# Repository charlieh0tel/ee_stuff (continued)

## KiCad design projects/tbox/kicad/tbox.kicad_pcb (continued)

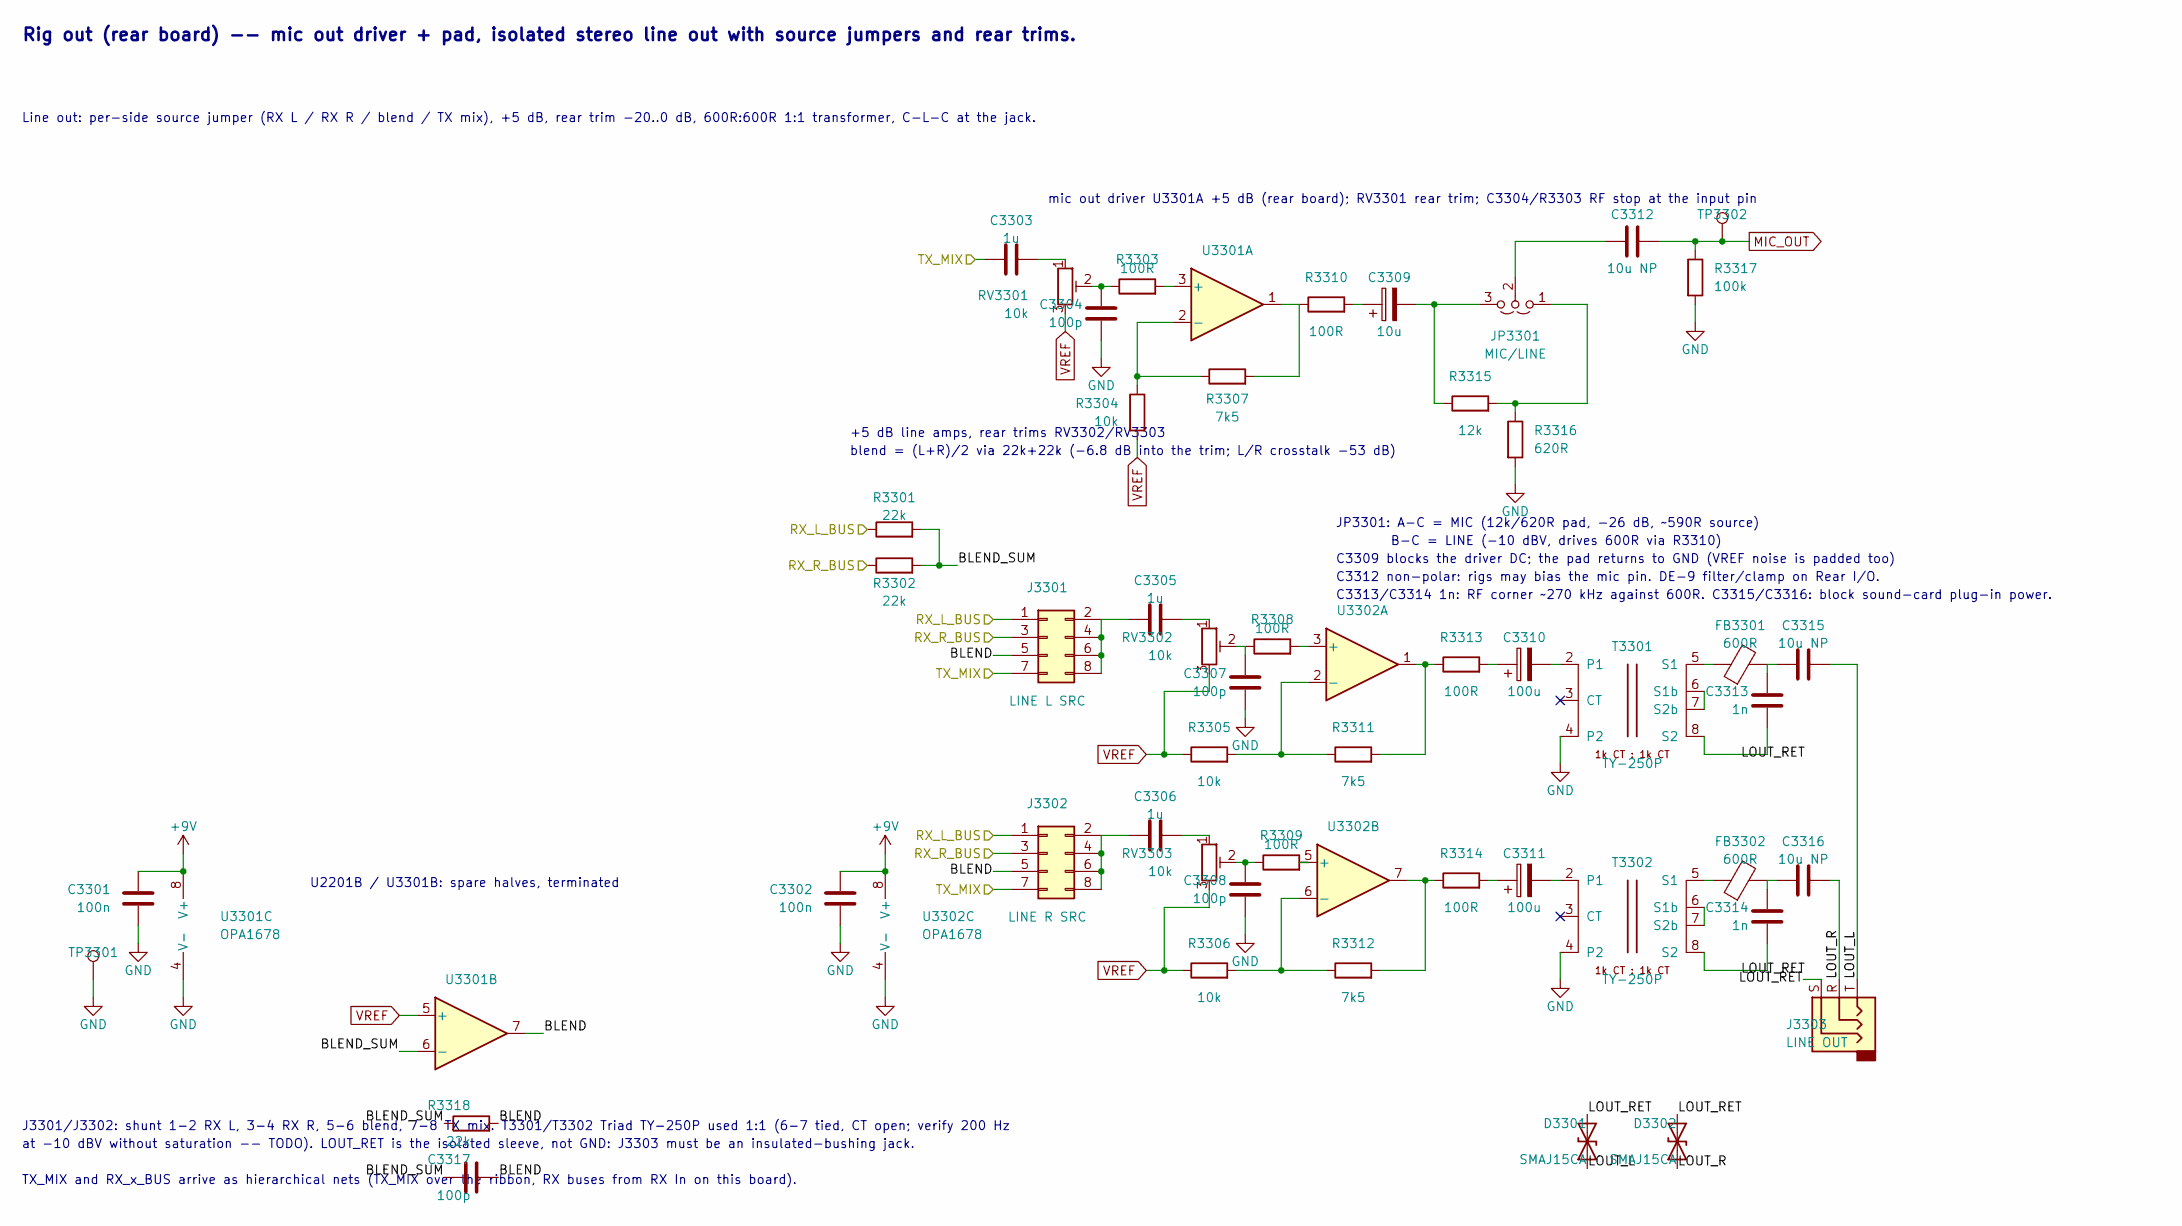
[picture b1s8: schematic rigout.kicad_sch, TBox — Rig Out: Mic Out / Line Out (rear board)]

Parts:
C3301, C3302: 100n; C_0603_1608Metric
C3303, C3305, C3306: 1u; C_0603_1608Metric
C3304, C3307, C3308, C3317: 100p; C_0603_1608Metric
C3309: 10u; CP_Elec_5x5.4
C3310, C3311: 100u; CP_Elec_6.3x7.7
C3312, C3315, C3316: 10u NP; C_1206_3216Metric
C3313, C3314: 1n; C_0603_1608Metric
D3301, D3302: SMAJ15CA; D_SMA; MPN SMAJ15CA
FB3301, FB3302: 600R; L_0805_2012Metric
J3301: LINE L SRC; PinHeader_2x04_P2.54mm_Vertical
J3302: LINE R SRC; PinHeader_2x04_P2.54mm_Vertical
J3303: LINE OUT; Jack_3.5mm_CUI_SJ1-3533NG_Horizontal; MPN SJ1-3533NG
JP3301: MIC/LINE; PinHeader_1x03_P2.54mm_Vertical
R3301, R3302, R3318: 22k; R_0603_1608Metric
R3303, R3308, R3309, R3310, R3313, R3314: 100R; R_0603_1608Metric
R3304, R3305, R3306: 10k; R_0603_1608Metric
R3307, R3311, R3312: 7k5; R_0603_1608Metric
R3315: 12k; R_0603_1608Metric
R3316: 620R; R_0603_1608Metric
R3317: 100k; R_0603_1608Metric
RV3301, RV3302, RV3303: 10k; Potentiometer_Bourns_3386W_Horizontal; MPN 3386W-1-103LF
T3301, T3302: TY-250P; Transformer_Triad_TY-250P; MPN TY-250P
TP3301: GND; TestPoint_Keystone_5015_Micro_Mini; MPN 5015
TP3302: MIC_OUT; TestPoint_Keystone_5015_Micro_Mini; MPN 5015
U3301, U3302: OPA1678; SOIC-8_3.9x4.9mm_P1.27mm; MPN OPA1678IDR

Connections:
+9V: C3301.1, C3302.1, U3301.8 (V+), U3302.8 (V+); also elsewhere on the board
/RX_L_BUS: J3301.1, J3302.1, R3301.1; also elsewhere on the board
/RX_R_BUS: J3301.3, J3302.3, R3302.1; also elsewhere on the board
/Rear Board/Rig Out/BLEND: C3317.2, J3301.5, J3302.5, R3318.2, U3301.7
/Rear Board/Rig Out/LOUT_L: C3315.2, D3301.1 (A1), J3303.T
/Rear Board/Rig Out/LOUT_R: C3316.2, D3302.1 (A1), J3303.R
/Rear Board/Rig Out/LOUT_RET: C3313.2, C3314.2, D3301.2 (A2), D3302.2 (A2), J3303.S, T3301.8 (S2), T3302.8 (S2)
/TX_MIX: C3303.1, J3301.7, J3302.7; also elsewhere on the board
MIC_OUT: C3312.2, R3317.1, TP3302.1 (1_1); also elsewhere on the board
unnamed: C3303.2, RV3301.1
unnamed: C3304.1, R3303.1, RV3301.2
unnamed: C3305.2, RV3302.1
unnamed: C3306.2, RV3303.1
unnamed: C3307.1, R3308.1, RV3302.2
unnamed: C3308.1, R3309.1, RV3303.2
unnamed: C3309.1, R3310.2
unnamed: C3310.1, R3313.2
unnamed: C3311.1, R3314.2
unnamed: C3313.1, C3315.1, FB3301.2
unnamed: C3314.1, C3316.1, FB3302.2
unnamed: C3305.1, J3301.2, J3301.4, J3301.6, J3301.8
unnamed: C3306.1, J3302.2, J3302.4, J3302.6, J3302.8
unnamed: JP3301.1 (A), R3315.2, R3316.1
unnamed: C3309.2, JP3301.3 (B), R3315.1
unnamed: C3312.1, JP3301.2 (C)
unnamed: R3307.2, R3310.1, U3301.1
unnamed: R3311.2, R3313.1, U3302.1
unnamed: R3312.2, R3314.1, U3302.7
unnamed: C3310.2, T3301.2 (P1)
unnamed: FB3301.1, T3301.5 (S1)
unnamed: T3301.6 (S1b), T3301.7 (S2b)
unnamed: C3311.2, T3302.2 (P1)
unnamed: FB3302.1, T3302.5 (S1)
unnamed: T3302.6 (S1b), T3302.7 (S2b)
unnamed: R3303.2, U3301.3 (+)
unnamed: R3304.1, R3307.1, U3301.2 (-)
unnamed: R3308.2, U3302.3 (+)
unnamed: R3305.2, R3311.1, U3302.2 (-)
unnamed: R3309.2, U3302.5 (+)
unnamed: R3306.2, R3312.1, U3302.6 (-)

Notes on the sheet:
J3301/J3302: shunt 1-2 RX L, 3-4 RX R, 5-6 blend, 7-8 TX mix. T3301/T3302 Triad TY-250P used 1:1 (6-7 tied, CT open; verify 200 Hz
at -10 dBV without saturation -- TODO). LOUT_RET is the isolated sleeve, not GND: J3303 must be an insulated-bushing jack.
B-C = LINE (-10 dBV, drives 600R via R3310)
C3312 non-polar: rigs may bias the mic pin. DE-9 filter/clamp on Rear I/O.
blend = (L+R)/2 via 22k+22k (-6.8 dB into the trim; L/R crosstalk -53 dB)
U2201B / U3301B: spare halves, terminated
+5 dB line amps, rear trims RV3302/RV3303
Rig out (rear board) -- mic out driver + pad, isolated stereo line out with source jumpers and rear trims.
TX_MIX and RX_x_BUS arrive as hierarchical nets (TX_MIX over the ribbon, RX buses from RX In on this board).
mic out driver U3301A +5 dB (rear board); RV3301 rear trim; C3304/R3303 RF stop at the input pin
Line out: per-side source jumper (RX L / RX R / blend / TX mix), +5 dB, rear trim -20..0 dB, 600R:600R 1:1 transformer, C-L-C at the jack.
C3309 blocks the driver DC; the pad returns to GND (VREF noise is padded too)
C3313/C3314 1n: RF corner ~270 kHz against 600R. C3315/C3316: block sound-card plug-in power.
JP3301: A-C = MIC (12k/620R pad, -26 dB, ~590R source)

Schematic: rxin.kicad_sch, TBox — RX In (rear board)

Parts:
C3401, C3402: 10u X7R 25V; C_1206_3216Metric; MPN GRM31CR71E106KA12L
C3403, C3404: 47u; CP_Elec_6.3x5.4
C3405, C3406: 100p; C_0603_1608Metric
C3407: 100n; C_0603_1608Metric
D3401, D3402, D3403, D3404: 1N4148W; D_SOD-123; MPN 1N4148W
R3403, R3404: 2k2; R_0603_1608Metric
R3405, R3406: 10k; R_0603_1608Metric
R3407, R3408: 100k; R_0603_1608Metric
R3409, R3410: 47k; R_0603_1608Metric
R3411, R3412: 100R; R_0603_1608Metric
RV3401, RV3402: 10k; Potentiometer_Bourns_3386W_Horizontal; MPN 3386W-1-103LF
TP3401: RX_L_BUS; TestPoint_Keystone_5015_Micro_Mini; MPN 5015
TP3402: RX_R_BUS; TestPoint_Keystone_5015_Micro_Mini; MPN 5015
U3401: OPA1678; SOIC-8_3.9x4.9mm_P1.27mm; MPN OPA1678IDR

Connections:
+9V: C3407.1, D3401.1 (K), D3403.1 (K), U3401.8 (V+); also elsewhere on the board
/RX_L_BUS: R3411.2, TP3401.1 (1_1); also elsewhere on the board
/RX_R_BUS: R3412.2, TP3402.1 (1_1); also elsewhere on the board
/Rear Board/RX In/RXA_AMP: C3405.1, D3401.2 (A), D3402.1 (K), R3403.2, R3407.2, U3401.3 (+)
/Rear Board/RX In/RXB_AMP: C3406.1, D3403.2 (A), D3404.1 (K), R3404.2, R3408.2, U3401.5 (+)
unnamed: C3401.1, R3403.1
unnamed: C3401.2, RV3401.2
unnamed: C3402.1, R3404.1
unnamed: C3402.2, RV3402.2
unnamed: C3403.1, R3405.1
unnamed: C3404.1, R3406.1
unnamed: R3409.2, R3411.1, U3401.1
unnamed: R3410.2, R3412.1, U3401.7
unnamed: R3405.2, R3409.1, U3401.2 (-)
unnamed: R3406.2, R3410.1, U3401.6 (-)
RX_L_IN: RV3401.1; also elsewhere on the board
RX_R_IN: RV3402.1; also elsewhere on the board

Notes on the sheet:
Max ~-0.4 dBV open (17 mW/32R, 22 mW/16R through the 10R build-out; one headset per position). 3.5 mm, 1/4" and the TRRS phones side (J1103/J1303 on the preamp sheets, via PH_x_L/R) are paralleled.
RX in (rear board) -- 10k bridging load, rear trims, +15 dB buffers -> RX_L_BUS / RX_R_BUS.
+15 dB (1 + 47k/10k), unity at DC (C3403/C3404); trims to GND, +in biased to VREF via 100k (VREF noise gain ~1); R3403/C3405 RF stop at the pin
RX in: the rear 10k trim to GND is the bridging load (hot phones-jack sources are simply trimmed down), AC-coupled into a +15 dB buffer -> RX_L_BUS / RX_R_BUS at -15 dBV.
Mono rig cables tie RX L and RX R at the DE-9 (Rear I/O sheet, with the filter/clamp).

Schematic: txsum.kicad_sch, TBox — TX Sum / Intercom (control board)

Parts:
C2201, C2202: 1u; C_0603_1608Metric
C2203, C2205: 100n; C_0603_1608Metric
C2204: 47p; C_0603_1608Metric
D2201: IC LED; LED_0805_2012Metric
Q2201: MMBT3904; SOT-23; MPN MMBT3904
Q2202: 2N7002; SOT-23; MPN 2N7002
R2201, R2202, R2203, R2204, R2206, R2208, R2209: 10k; R_0603_1608Metric
R2205: 20k; R_0603_1608Metric
R2207: 100R; R_0603_1608Metric
R2210: 2k2; R_0805_2012Metric
R2211: 100k; R_0603_1608Metric
RV2201, RV2202: 10k; Potentiometer_Alpha_RD901F-40-00D_Single_Vertical; MPN RD901F-40-15R1-A10K
SW2201: INTERCOM; SW_Push_2P1T_Toggle_CK_PVA1xxH2xxxxxxV2; MPN PVA1OAH2xxxxxxV2 (OA = momentary; heigh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
TP2201: TX_MIX; TestPoint_Keystone_5015_Micro_Mini; MPN 5015
TP2202: CH_A_OUT; TestPoint_Keystone_5015_Micro_Mini; MPN 5015
TP2203: CH_B_OUT; TestPoint_Keystone_5015_Micro_Mini; MPN 5015
U2201: OPA1678; SOIC-8_3.9x4.9mm_P1.27mm; MPN OPA1678IDR

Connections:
+9V: C2205.1, R2201.1, R2208.1, U2201.8 (V+); also elsewhere on the board
/Control Board/TX Sum / Intercom/CH_A_OUT: C2201.1, RV2201.2, TP2202.1 (1_1)
/Control Board/TX Sum / Intercom/CH_B_OUT: C2202.1, RV2202.2, TP2203.1 (1_1)
/PRE_A_OUT: RV2201.1; also elsewhere on the board
/PRE_B_OUT: RV2202.1; also elsewhere on the board
/PTT_ACTIVE: R2206.1; also elsewhere on the board
/TX_MIX: R2211.1, TP2201.1 (1_1); also elsewhere on the board
unnamed: C2201.2, R2202.1
unnamed: C2202.2, R2203.1
unnamed: C2203.1, R2201.2, R2204.1, SW2201.2
unnamed: C2204.2, R2205.2, R2207.1, U2201.1
unnamed: D2201.2 (A), R2210.2
unnamed: D2201.1 (K), Q2202.3 (D)
unnamed: Q2201.1 (B), R2204.2, R2206.2
unnamed: Q2202.1 (G), R2209.2
unnamed: C2204.1, R2202.2, R2203.2, R2205.1, U2201.2 (-)
unnamed: U2201.6 (-), U2201.7
TX_MON: R2207.2; also elsewhere on the board

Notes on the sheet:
R2207 isolates the cap load
post-mute TX mix (line level; crosses to rear board)
Intercom: momentary, mutes TX downstream of the monitor tap; locked out while PTT_ACTIVE=1 (Keying Logic sheet). Control lines are DC logic 0/+9V, active high.
+6 dB inverting sum (Rf/Rin = 2)
Levels (LEVELS.md): level-pot wipers -21 dBV -> sum +6 dB -> -15 dBV. Mic out: +5 dB driver, rear trim -20..0 dB, MIC pad -26 dB (~590R source) or LINE direct.
Level pots RV2201/RV2202 (top panel) live here: PRE_x_OUT arrives at line level over the ribbon; the wiper feeds the sum locally.
Bus order: sum -> TX_MON (monitor pots, Monitor/Phones sheet) -> intercom mute -> TX_MIX -> mic out pad / line out TX tap.
LEVEL A (top panel), audio taper; -21 dBV at design centre
LEVEL B (top panel), audio taper; -21 dBV at design centre
LED from the raw rail (droppers), never from +9V
Hierarchical: PRE_x_OUT from the front board (ribbon), TX_MIX to the rear board, PTT_ACTIVE from Keying Logic.
TX sum / intercom (control board) -- channel level pots, summing amp, monitor tap, intercom mute + logic.
IC_MUTE = NOT(button up OR PTT_ACTIVE): pressed & not keyed -> mute

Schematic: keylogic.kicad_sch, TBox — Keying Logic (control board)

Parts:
C2101, C2102: 100n; C_0603_1608Metric
D2101: TX; LED_0805_2012Metric
D2102: PTT A; LED_0805_2012Metric
D2103, D2104, D2105, D2106, D2109, D2110, D2111, D2112, D2113, D2114, D2115, D2116, D2120, D2121: 1N4148W; D_SOD-123; MPN 1N4148W
D2107: PTT B; LED_0805_2012Metric
D2108: MUTE A; LED_0805_2012Metric
D2117: MUTE B; LED_0805_2012Metric
D2118: PWR; LED_0805_2012Metric
JP2101, JP2102: PTT GATE; PinHeader_1x02_P2.54mm_Vertical
Q2101, Q2102, Q2103, Q2104, Q2105, Q2106, Q2107, Q2108, Q2109: 2N7002; SOT-23; MPN 2N7002
R2101, R2103, R2107, R2108, R2109, R2113, R2118, R2122: 10k; R_0603_1608Metric
R2102, R2106, R2110, R2114, R2119, R2120: 2k2; R_0805_2012Metric
R2104, R2105, R2115, R2116: 1k; R_0603_1608Metric
R2111, R2112: 2k2; R_0603_1608Metric
R2117: 47k; R_0603_1608Metric
SW2101: PTT A; SW_Push_2P1T_Toggle_CK_PVA1xxH2xxxxxxV2; MPN PVA1OAH2xxxxxxV2 (OA = momentary; heigh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
SW2102: PTT B; SW_Push_2P1T_Toggle_CK_PVA1xxH2xxxxxxV2; MPN PVA1OAH2xxxxxxV2 (OA = momentary; heigh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
SW2103: OVERRIDE; SW_Toggle_CK_7201_V-Bracket_Vertical; MPN 7203MD9V6BE
SW2104: MUTE A; SW_Push_2P1T_Toggle_CK_PVA1xxH2xxxxxxV2; MPN PVA1EEH2xxxxxxV2 (EE = push-push latchi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
SW2105: MUTE B; SW_Push_2P1T_Toggle_CK_PVA1xxH2xxxxxxV2; MPN PVA1EEH2xxxxxxV2 (EE = push-push latchi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
TP2101: PTT_ACTIVE; TestPoint_Keystone_5015_Micro_Mini; MPN 5015
TP2102: MUTE_A; TestPoint_Keystone_5015_Micro_Mini; MPN 5015
TP2103: MUTE_B; TestPoint_Keystone_5015_Micro_Mini; MPN 5015
TP2104: GND; TestPoint_Keystone_5015_Micro_Mini; MPN 5015

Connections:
+9V: D2103.1 (K), D2105.1 (K), R2111.1, R2112.1, R2115.1, R2116.1, R2122.1; also elsewhere on the board
/Control Board/Keying Logic/MUTE_HOLD: D2120.2 (A), D2121.2 (A), Q2108.3 (D), Q2109.1 (G), R2122.2
/Control Board/Keying Logic/OVR_A: D2111.2 (A), SW2103.6 (C)
/Control Board/Keying Logic/OVR_B: D2114.2 (A), SW2103.1 (A)
/Control Board/Keying Logic/PTT_A: D2109.2 (A), Q2104.3 (D), R2103.1, R2111.2, SW2103.2 (B)
/Control Board/Keying Logic/PTT_A_N: C2101.1, D2103.2 (A), D2104.1 (K), JP2101.1 (A), R2104.2, R2108.1
/Control Board/Keying Logic/PTT_B: D2110.2 (A), Q2105.3 (D), R2107.1, R2112.2, SW2103.5 (B)
/Control Board/Keying Logic/PTT_B_N: C2102.1, D2105.2 (A), D2106.1 (K), JP2102.1 (A), R2105.2, R2109.1
/MUTE_B: D2114.1 (K), D2115.1 (K), D2116.1 (K), D2121.1 (K), R2118.1, TP2103.1 (1_1); also elsewhere on the board
/PTT_ACTIVE: D2109.1 (K), D2110.1 (K), Q2109.3 (D), R2101.1, R2117.1, TP2101.1 (1_1); also elsewhere on the board
/PTT_A_IN: R2104.1, SW2101.2; also elsewhere on the board
/PTT_B_IN: R2105.1, SW2102.2; also elsewhere on the board
unnamed: D2101.2 (A), R2102.2
unnamed: D2101.1 (K), Q2101.3 (D)
unnamed: D2102.2 (A), R2106.2
unnamed: D2102.1 (K), Q2102.3 (D)
unnamed: D2107.2 (A), R2110.2
unnamed: D2107.1 (K), Q2103.3 (D)
unnamed: D2108.2 (A), R2114.2
unnamed: D2108.1 (K), Q2106.3 (D)
unnamed: D2112.2 (A), SW2104.2 (B)
unnamed: D2113.2 (A), JP2101.2 (B)
unnamed: D2115.2 (A), SW2105.2 (B)
unnamed: D2116.2 (A), JP2102.2 (B)
unnamed: D2117.2 (A), R2119.2
unnamed: D2117.1 (K), Q2107.3 (D)
unnamed: D2118.2 (A), R2120.2
unnamed: Q2101.1 (G), R2101.2
unnamed: Q2102.1 (G), R2103.2
unnamed: Q2103.1 (G), R2107.2
unnamed: Q2104.1 (G), R2108.2
unnamed: Q2105.1 (G), R2109.2
unnamed: Q2106.1 (G), R2113.2
unnamed: Q2107.1 (G), R2118.2
unnamed: R2115.2, SW2104.1 (A)
unnamed: R2116.2, SW2105.1 (A)
PWR_OK: Q2108.1 (G); also elsewhere on the board

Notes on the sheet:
INDICATORS: TX lamp (17 mA, prominent), per-channel PTT and MUTE, power. Intercom LED is on the TX Sum sheet.
both mutes on through D2120/D2121, PTT_ACTIVE shunted by Q2109, phones amps disabled.
Keying logic (control board) -- PTT inputs from the rear jacks + top-panel buttons, override / mute logic, indicators, power-on hold.
Logic (0/+9V, active high): PTT_x = keyed (2k2 pull-up, ~7.4 V loaded); PTT_ACTIVE = A or B (~6.8 V) -> 2N7002 open-drain to the rig, intercom lockout, TX lamp.
All LEDs run from the raw filtered rail so their step loads never touch the +9V analog rail.
Power-on / brown-out hold: PWR_OK (TPS3808, Supply sheet) low -> Q2108 raises MUTE_HOLD:
OVERRIDE (SW2103, on-off-on): A->B / centre OFF / B->A as marked on the top panel
JP2101/JP2102 (PTT GATE): mic live only while keyed
OVERRIDE (DPDT on-off-on, top panel): A->B keys the rig from A and mutes B; B->A mirror. MUTE_x = latching button OR override OR (JP70x: not keyed) OR power-on hold. All logic transistors are 2N7002 so no base current loads the logic highs.

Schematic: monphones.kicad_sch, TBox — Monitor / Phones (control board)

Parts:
C2401, C2402, C2408, C2409: 470u; CP_Elec_10x10.5
C2405, C2407: 220u; CP_Elec_8x10.5
C2406, C2410, C2413: 100n; C_0603_1608Metric
H2401: CHASSIS STUD; MountingHole_3.2mm_M3_Pad
NT2401: GND-CHASSIS tie; NetTie-2_SMD_Pad0.5mm
R2401, R2402, R2403, R2404, R2405, R2406, R2413, R2414, R2415, R2416, R2417, R2418: 10k; R_0603_1608Metric
R2407, R2408, R2419, R2420: 150k; R_0603_1608Metric
R2409, R2410, R2421, R2422: 3R3; R_0603_1608Metric
R2411, R2412, R2423, R2424: 4k7; R_0603_1608Metric
RV2401, RV2404: 10k dual; Potentiometer_Alpha_RD902F-40-00D_Dual_Vertical; MPN RD902F-40-15R1-A10K
RV2402, RV2403: 10k; Potentiometer_Alpha_RD901F-40-00D_Single_Vertical; MPN RD901F-40-15R1-A10K
TP2401: GND; TestPoint_Keystone_5015_Micro_Mini; MPN 5015
U2401, U2403: OPA1622; Texas_DRC0010J; MPN OPA1622IDRCR
U2402: OPA1678; SOIC-8_3.9x4.9mm_P1.27mm; MPN OPA1678IDR

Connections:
+9V: C2405.1, C2406.1, C2407.1, C2410.1, C2413.1, U2401.2 (V+), U2402.8 (V+), U2403.2 (V+); also elsewhere on the board
/Control Board/Monitor / Phones/MON_A: R2402.1, R2404.1, U2402.1, U2402.2 (-)
/Control Board/Monitor / Phones/MON_B: R2414.1, R2416.1, U2402.6 (-), U2402.7
/PH_A_L: C2401.2, R2411.1; also elsewhere on the board
/PH_A_R: C2402.2, R2412.1; also elsewhere on the board
/PH_B_L: C2408.2, R2423.1; also elsewhere on the board
/PH_B_R: C2409.2, R2424.1; also elsewhere on the board
/RX_L_BUS: R2401.1, R2413.1; also elsewhere on the board
/RX_R_BUS: R2403.1, R2415.1; also elsewhere on the board
unnamed 80: C2401.1, R2409.2; also elsewhere on the board
unnamed 81: C2402.1, R2410.2; also elsewhere on the board
unnamed 82: C2408.1, R2421.2; also elsewhere on the board
unnamed 83: C2409.1, R2422.2; also elsewhere on the board
unnamed: R2401.2, R2402.2, RV2401.1
unnamed: R2403.2, R2404.2, RV2401.4
unnamed: R2407.2, R2409.1, U2401.9
unnamed: R2408.2, R2410.1, U2401.7
unnamed: R2413.2, R2414.2, RV2404.1
unnamed: R2415.2, R2416.2, RV2404.4
unnamed: R2419.2, R2421.1, U2403.9
unnamed: R2420.2, R2422.1, U2403.7
unnamed: RV2401.2, U2401.1 (+)
unnamed: R2405.1, R2407.1, U2401.10 (-)
unnamed: RV2401.5, U2401.5 (+)
unnamed: R2406.1, R2408.1, U2401.6 (-)
unnamed: RV2402.2, U2402.3 (+)
unnamed: RV2403.2, U2402.5 (+)
unnamed: RV2404.2, U2403.1 (+)
unnamed: R2417.1, R2419.1, U2403.10 (-)
unnamed: RV2404.5, U2403.5 (+)
unnamed: R2418.1, R2420.1, U2403.6 (-)
PWR_OK: U2401.8 (EN), U2403.8 (EN); also elsewhere on the board
TX_MON: RV2402.1, RV2403.1; also elsewhere on the board

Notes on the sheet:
Hierarchical: RX_x_BUS from the rear board (ribbon); PH_x_L/R to the front board (ribbon). TX_MON is board-local from TX Sum.
POSITION A
MON pots: front panel, per position
OPA1622: 150 mA output, drives 16R phones from 9 V; EN = PWR_OK (click-free enable), PAD = V-
RV2401/RV2404: dual-gang volume; all pots return to VREF (no DC on wipers).
Monitor: TX_MON (pre-intercom) -> front MON pot per position -> unity buffer -> MON_A / MON_B (off .. -15 dBV).
C2405/C2407: +9V bulk next to U2401/U2403 (class-B return current)
POSITION B
Monitor / phones (control board) -- MON pots and buffers, per-ear passive mix, VOL, NJM4556A headphone amps -> front-board jacks.
Each ear: RX side + MON summed passively (10k+10k into the 10k volume gang, -9.5 dB) -> NJM4556A +24 dB -> 10R -> 470u -> bead + 10n -> PH_x_L/R over the ribbon to the front-board jacks (sleeves to GND).

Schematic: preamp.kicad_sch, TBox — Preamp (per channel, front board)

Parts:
C1101, C1109: 1n; C_0603_1608Metric
C1102, C1107, C1108: 100n; C_0603_1608Metric
C1103: 1u; C_0603_1608Metric
C1104: 100p; C_0603_1608Metric
C1105, C1106: 47u; CP_Elec_6.3x5.4
FB1101, FB1102, FB1103: 600R; L_0805_2012Metric
J1101: MIC 3.5; Jack_3.5mm_Switchcraft_35RAPCxxH3_Horizontal; MPN 35RAPC2BH3
J1102: MIC 1/4; Jack_6.35mm_Neutrik_NRJ6HM-1-PRE_Horizontal; MPN NRJ6HM-1-PRE
J1103: HEADSET; Jack_3.5mm_CUI_SJ-43514_Horizontal; MPN SJ-43514
J1104: SPARE; JST_XH_B4B-XH-A_1x04_P2.50mm_Vertical; MPN B4B-XH-A
R1101, R1109: 2k2; R_0603_1608Metric
R1102: 47k; R_0603_1608Metric
R1103: 100R; R_0603_1608Metric
R1104: 430R; R_0603_1608Metric
R1105, R1107: 10k; R_0603_1608Metric
R1106: 3k3; R_0603_1608Metric
R1108: 100k; R_0603_1608Metric
TP1101: GND; TestPoint_Keystone_5015_Micro_Mini; MPN 5015
U1101: OPA1678; SOIC-8_3.9x4.9mm_P1.27mm; MPN OPA1678IDR
U1102: TS12A12511; MSOP-8_3x3mm_P0.65mm; MPN TS12A12511DGKR
U1103, U1104: SP724; SOT-23-6; MPN SP724AHTG

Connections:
+9V: C1107.1, C1108.1, J1104.4, U1101.8 (V+), U1102.4 (V+), U1103.5 (V+), U1104.5 (V+); also elsewhere on the board
/BIAS_A: C1102.1, J1104.2, R1101.1, R1109.1; also elsewhere on the board
/Front Board/PHJ_A_L: J1103.T, U1104.1 (IN1); also elsewhere on the board
/Front Board/PHJ_A_R: J1103.R1, U1104.3 (IN2); also elsewhere on the board
/Front Board/Preamp A/HS_MIC: FB1103.1, J1103.S, U1103.6 (IN4)
/Front Board/Preamp A/MIC: C1101.1, C1103.1, FB1101.2, FB1102.2, FB1103.2, J1104.1, R1101.2
/Front Board/Preamp A/MIC14T: FB1102.1, J1102.T, U1103.4 (IN3)
/Front Board/Preamp A/MIC35T: FB1101.1, J1101.T, U1103.1 (IN1)
/Front Board/Preamp A/MIC_R: C1109.1, J1101.R, R1109.2, U1103.3 (IN2)
/Front Board/Preamp A/Mute/IN: U1102.1 (COM); also elsewhere on the board
/GAIN_A_HI: R1108.1, U1102.6 (IN); also elsewhere on the board
unnamed: C1103.2, R1102.1, R1103.1
unnamed: C1105.1, R1104.2
unnamed: C1106.1, R1106.2
unnamed: C1104.1, R1103.2, U1101.3 (+)
unnamed: R1104.1, R1105.1, U1101.2 (-)
unnamed: R1105.2, U1101.1, U1101.5 (+), U1102.2 (NC)
unnamed: R1106.1, R1107.1, U1101.6 (-)
unnamed: R1107.2, U1101.7, U1102.8 (NO)

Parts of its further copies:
C1301, C1309: 1n; C_0603_1608Metric
C1302, C1307, C1308: 100n; C_0603_1608Metric
C1303: 1u; C_0603_1608Metric
C1304: 100p; C_0603_1608Metric
C1305, C1306: 47u; CP_Elec_6.3x5.4
FB1301, FB1302, FB1303: 600R; L_0805_2012Metric
J1301: MIC 3.5; Jack_3.5mm_Switchcraft_35RAPCxxH3_Horizontal; MPN 35RAPC2BH3
J1302: MIC 1/4; Jack_6.35mm_Neutrik_NRJ6HM-1-PRE_Horizontal; MPN NRJ6HM-1-PRE
J1303: HEADSET; Jack_3.5mm_CUI_SJ-43514_Horizontal; MPN SJ-43514
J1304: SPARE; JST_XH_B4B-XH-A_1x04_P2.50mm_Vertical; MPN B4B-XH-A
R1301, R1309: 2k2; R_0603_1608Metric
R1302: 47k; R_0603_1608Metric
R1303: 100R; R_0603_1608Metric
R1304: 430R; R_0603_1608Metric
R1305, R1307: 10k; R_0603_1608Metric
R1306: 3k3; R_0603_1608Metric
R1308: 100k; R_0603_1608Metric
TP1301: GND; TestPoint_Keystone_5015_Micro_Mini; MPN 5015
U1301: OPA1678; SOIC-8_3.9x4.9mm_P1.27mm; MPN OPA1678IDR
U1302: TS12A12511; MSOP-8_3x3mm_P0.65mm; MPN TS12A12511DGKR
U1303, U1304: SP724; SOT-23-6; MPN SP724AHTG

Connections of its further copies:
+9V: C1307.1, C1308.1, J1304.4, U1301.8 (V+), U1302.4 (V+), U1303.5 (V+), U1304.5 (V+); also elsewhere on the board
/BIAS_B: C1302.1, J1304.2, R1301.1, R1309.1; also elsewhere on the board
/Front Board/PHJ_B_L: J1303.T, U1304.1 (IN1); also elsewhere on the board
/Front Board/PHJ_B_R: J1303.R1, U1304.3 (IN2); also elsewhere on the board
/Front Board/Preamp B/HS_MIC: FB1303.1, J1303.S, U1303.6 (IN4)
/Front Board/Preamp B/MIC: C1301.1, C1303.1, FB1301.2, FB1302.2, FB1303.2, J1304.1, R1301.2
/Front Board/Preamp B/MIC14T: FB1302.1, J1302.T, U1303.4 (IN3)
/Front Board/Preamp B/MIC35T: FB1301.1, J1301.T, U1303.1 (IN1)
/Front Board/Preamp B/MIC_R: C1309.1, J1301.R, R1309.2, U1303.3 (IN2)
/Front Board/Preamp B/Mute/IN: U1302.1 (COM); also elsewhere on the board
/GAIN_B_HI: R1308.1, U1302.6 (IN); also elsewhere on the board
unnamed: C1303.2, R1302.1, R1303.1
unnamed: C1305.1, R1304.2
unnamed: C1306.1, R1306.2
unnamed: C1304.1, R1303.2, U1301.3 (+)
unnamed: R1304.1, R1305.1, U1301.2 (-)
unnamed: R1305.2, U1301.1, U1301.5 (+), U1302.2 (NC)
unnamed: R1306.1, R1307.1, U1301.6 (-)
unnamed: R1307.2, U1301.7, U1302.8 (NO)

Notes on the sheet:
Mute: TS12A12511 SPDT to VREF on the shared Mute sheet (>70 dB, no DC across it); MUTE=1 mutes.
C1105/C1106 return to GND, not VREF: the mic is ground-referenced, so a VREF-referenced feedback leg would amplify VREF noise by the full stage gain.
stage 1: +20 dB
GAIN_HI=1 -> +40 dB
Cascade gain: TS12A12511 (2.7-12 V SPDT) selects stage output into >=10k load (Ron out of feedback).
R1103/C1104: RF stop at the +40 dB input pin. C1102 decouples the bias line where it enters the mic node. Mic jack sleeves bond to CHASSIS at entry (single CHASSIS-GND tie on Rear I/O); the TRRS common (ring 2) is GND so the headset's phones current returns on the board.
Mic preamp -- one file, two instances (Preamp A / Preamp B).
stage 2: +20 dB (total +40)
Mic inputs: 3 jacks paralleled -- plug exactly one. TRRS is CTIA: sleeve=mic, ring2=common (GND).
spare mic tap (Foster retrofit)

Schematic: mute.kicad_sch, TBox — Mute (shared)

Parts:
C1201, C2302: 100n; C_0603_1608Metric
C2303: 1u; C_0603_1608Metric
D2301: 1N4148W; D_SOD-123; MPN 1N4148W-7-F
Q2301, Q2302: 2N7002; SOT-23; MPN 2N7002
Q2303, Q2304: 2N7002; SOT-23; MPN 2N7002-7-F
R1201, R2304, R2305: 100k; R_0603_1608Metric
R2302: 220R; R_0603_1608Metric
R2303: 47k; R_0603_1608Metric
R2306: 470k; R_0603_1608Metric
U1201: TS12A12511; MSOP-8_3x3mm_P0.65mm; MPN TS12A12511DGKR

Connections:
+9V: C1201.1, R2305.1, U1201.4 (V+); also elsewhere on the board
/Control Board/TX Sum / Intercom/Intercom Mute/FADE_S: Q2301.2 (S), Q2302.2 (S)
/Control Board/TX Sum / Intercom/Intercom Mute/MUTE_N: Q2303.3 (D), Q2304.1 (G), R2305.2
/PRE_A_OUT: U1201.1 (COM); also elsewhere on the board
unnamed: D2301.1 (K), R2303.1
TX_MON: R2302.1; also elsewhere on the board

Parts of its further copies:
C1203, C1403: 1u; C_0603_1608Metric
C1401, C2301: 100n; C_0603_1608Metric
D1201, D1401: 1N4148W; D_SOD-123; MPN 1N4148W-7-F
Q1204, Q1404: 2N7002; SOT-23; MPN 2N7002-7-F
R1202, R1402: 220R; R_0603_1608Metric
R1205, R1401, R1405, R2301: 100k; R_0603_1608Metric
U1401, U2301: TS12A12511; MSOP-8_3x3mm_P0.65mm; MPN TS12A12511DGKR

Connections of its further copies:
+9V: C1401.1, C2301.1, R1205.1, R1405.1, U1401.4 (V+), U2301.4 (V+); also elsewhere on the board
/Front Board/Preamp A/Mute/IN: R1202.1; also elsewhere on the board
/Front Board/Preamp A/Mute/MUTE_DRV: D1201.2 (A), Q1204.3 (D); also elsewhere on the board
/Front Board/Preamp A/Mute/MUTE_N: Q1204.1 (G), R1205.2; also elsewhere on the board
/Front Board/Preamp B/Mute/FADE: R1402.2, U1401.2 (NC); also elsewhere on the board
/Front Board/Preamp B/Mute/IN: R1402.1; also elsewhere on the board
/Front Board/Preamp B/Mute/MUTE_DRV: D1401.2 (A), Q1404.3 (D); also elsewhere on the board
/Front Board/Preamp B/Mute/MUTE_N: Q1404.1 (G), R1405.2; also elsewhere on the board
/Front Board/Preamp B/Mute/SW_CTL: C1403.1, U1401.6 (IN); also elsewhere on the board
/MUTE_B: R1401.1; also elsewhere on the board
/PRE_B_OUT: U1401.1 (COM); also elsewhere on the board
/TX_MIX: U2301.1 (COM); also elsewhere on the board
unnamed 103: D1201.1 (K); also elsewhere on the board
unnamed 105: D1401.1 (K); also elsewhere on the board

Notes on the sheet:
Mute -- TS12A12511 SPDT analog switch. One file, three instances (Preamp A, Preamp B, Intercom).
Control input: VIH guaranteed 2.4 V (10 V supply) / 5 V (12 V supply), ~1.5 V typ; every MUTE source in this design sits >= 6 V loaded. MUTE is a diode-OR of source-only drivers with a 100k pull-down (R1201): nothing here discharges through it.
MUTE=1 (0/+9V logic) selects NO: OUT is clamped to VREF and IN is isolated (off isolation -70 dB at 1 MHz, far better at audio). MUTE=0 passes IN via NC (Ron ~5 ohm, break-before-make ~30 ns).
V- to GND (single supply); thermal pad to GND or floating.
NC = signal, NO = VREF, COM = OUT
No DC across the switch: IN comes from a VREF-referenced stage with unity DC gain and the OUT load returns to VREF, so the switching step is only the op-amp Vos (a few mV, -48 dBV) -- no pop.

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
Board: 4 copper layers, 440 parts (0 on the bottom side), 229 nets, no tracks yet.

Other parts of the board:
C1110, C1111, C1310, C1311, C3208: 100n; C_0603_1608Metric
C1202, C1402: 470n; C_0603_1608Metric
D1202, D1402, D2302: 1N4148W; D_SOD-123
Q1201, Q1202, Q1401, Q1402: PMV30UN2; SOT-23
Q1203, Q1403: BSS138BK; SOT-23
R1203, R1403: 4k7; R_0603_1608Metric
R1204, R1404: 470k; R_0603_1608Metric
R1206, R1406: 100k; R_0603_1608Metric
R1207, R1407, R2307: 2k2; R_0603_1608Metric
R1208, R1408, R2308: 220R; R_0603_1608Metric
R2425, R2426, R2427, R2428: 1k; R_0603_1608Metric
R3319: 22k; R_0603_1608Metric

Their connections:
+9V: C1110.1, C1111.1, C1310.1, C1311.1, C3208.1, R1207.1, R1407.1, R2307.1; also elsewhere on the board
/Front Board/Preamp A/Mute/FADE_G: C1202.1, Q1201.1 (G), Q1202.1 (G), R1203.2, R1206.2
/Front Board/Preamp A/Mute/FADE_S: Q1201.2 (S), Q1202.2 (S)
/Front Board/Preamp A/Mute/MUTE_DRV: D1202.1 (K), R1204.1, R1206.1, R1207.2; also elsewhere on the board
/Front Board/Preamp A/Mute/MUTE_N: Q1203.3 (D); also elsewhere on the board
/Front Board/Preamp B/Mute/FADE: Q1401.3 (D); also elsewhere on the board
/Front Board/Preamp B/Mute/FADE_G: C1402.1, Q1401.1 (G), Q1402.1 (G), R1403.2, R1406.2
/Front Board/Preamp B/Mute/FADE_S: Q1401.2 (S), Q1402.2 (S)
/Front Board/Preamp B/Mute/MUTE_DRV: D1402.1 (K), R1404.1, R1406.1, R1407.2; also elsewhere on the board
/Front Board/Preamp B/Mute/MUTE_N: Q1403.3 (D); also elsewhere on the board
/Front Board/Preamp B/Mute/SW_CTL: R1404.2, R1408.2; also elsewhere on the board
/MUTE_B: Q1403.1 (G); also elsewhere on the board
unnamed 80: R2425.2; also elsewhere on the board
unnamed 81: R2426.2; also elsewhere on the board
unnamed 82: R2427.2; also elsewhere on the board
unnamed 83: R2428.2; also elsewhere on the board
unnamed 103: R1203.1; also elsewhere on the board
unnamed: D1202.2 (A), R1208.1
unnamed 105: R1403.1; also elsewhere on the board
unnamed: D1402.2 (A), R1408.1
unnamed: D2302.2 (A), R2308.1

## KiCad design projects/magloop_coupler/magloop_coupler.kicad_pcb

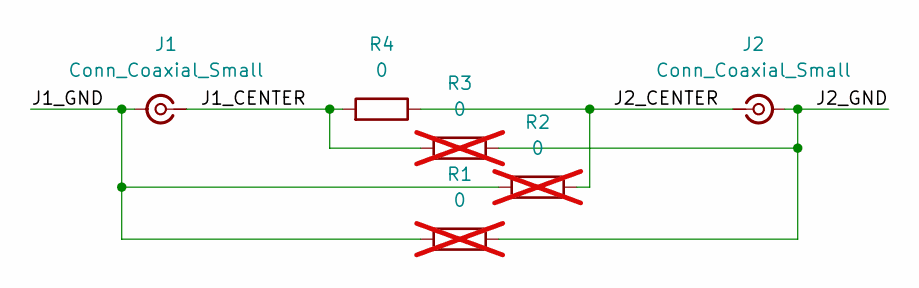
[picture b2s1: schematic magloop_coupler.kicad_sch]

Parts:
J1, J2: Conn_Coaxial_Small; SMA_Amphenol_132203-12_Horizontal
R1, R2, R3: 0; R_0805_2012Metric_Pad1.20x1.40mm_HandSolder; not fitted
R4: 0; R_0805_2012Metric_Pad1.20x1.40mm_HandSolder

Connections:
/J1_CENTER: J1.1 (In), R3.1, R4.2
/J1_GND: J1.2 (Ext), R1.1, R2.1
/J2_CENTER: J2.1 (In), R2.2, R4.1
/J2_GND: J2.2 (Ext), R1.2, R3.2

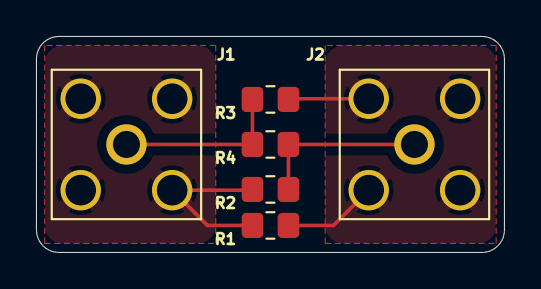
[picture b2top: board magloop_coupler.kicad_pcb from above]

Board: 2 copper layers, 26.0 x 12.0 mm, 6 parts (0 on the bottom side), 4 nets.

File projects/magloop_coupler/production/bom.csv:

Designator,Footprint,Quantity,Value,LCSC Part #
"J1, J2",SMA_Amphenol_132203-12_Horizontal,2,Conn_Coaxial_Small,
R4,0805,1,0,
